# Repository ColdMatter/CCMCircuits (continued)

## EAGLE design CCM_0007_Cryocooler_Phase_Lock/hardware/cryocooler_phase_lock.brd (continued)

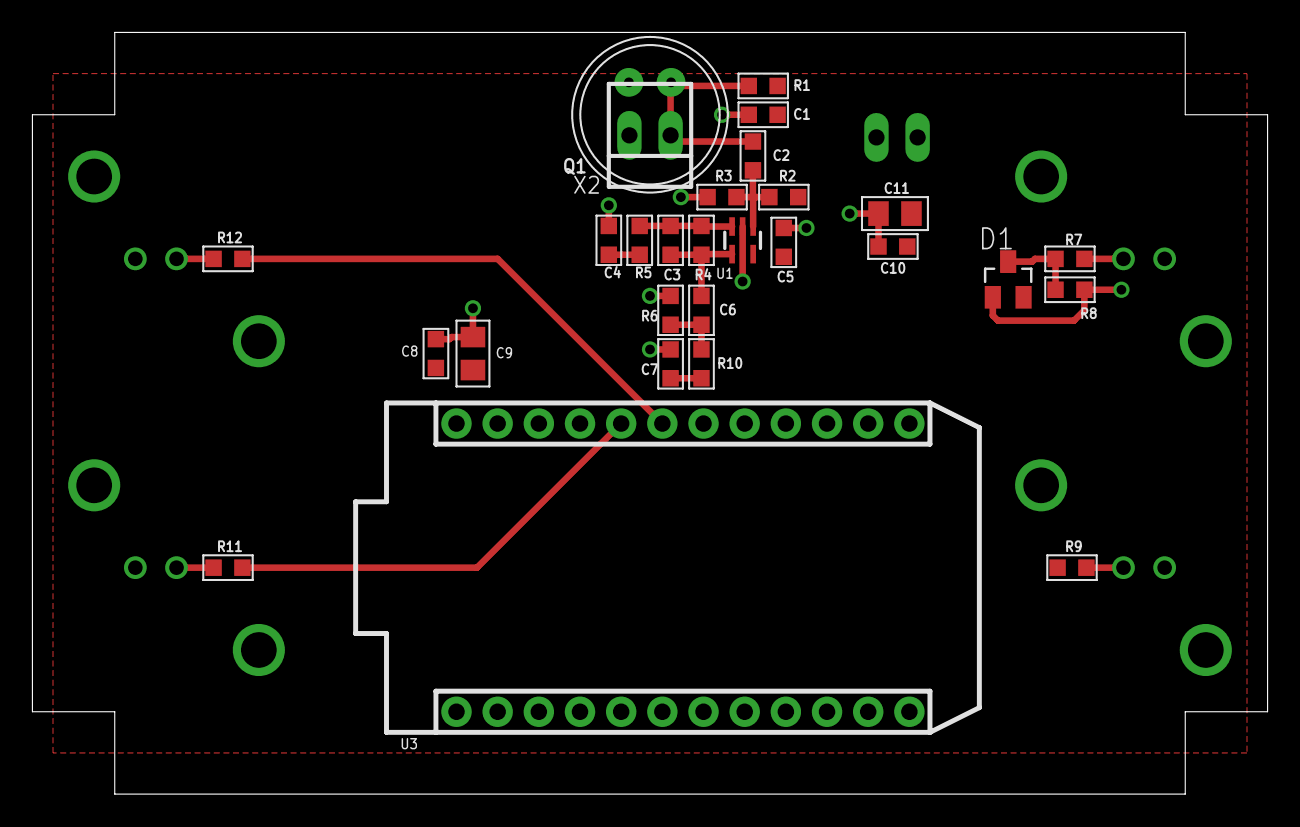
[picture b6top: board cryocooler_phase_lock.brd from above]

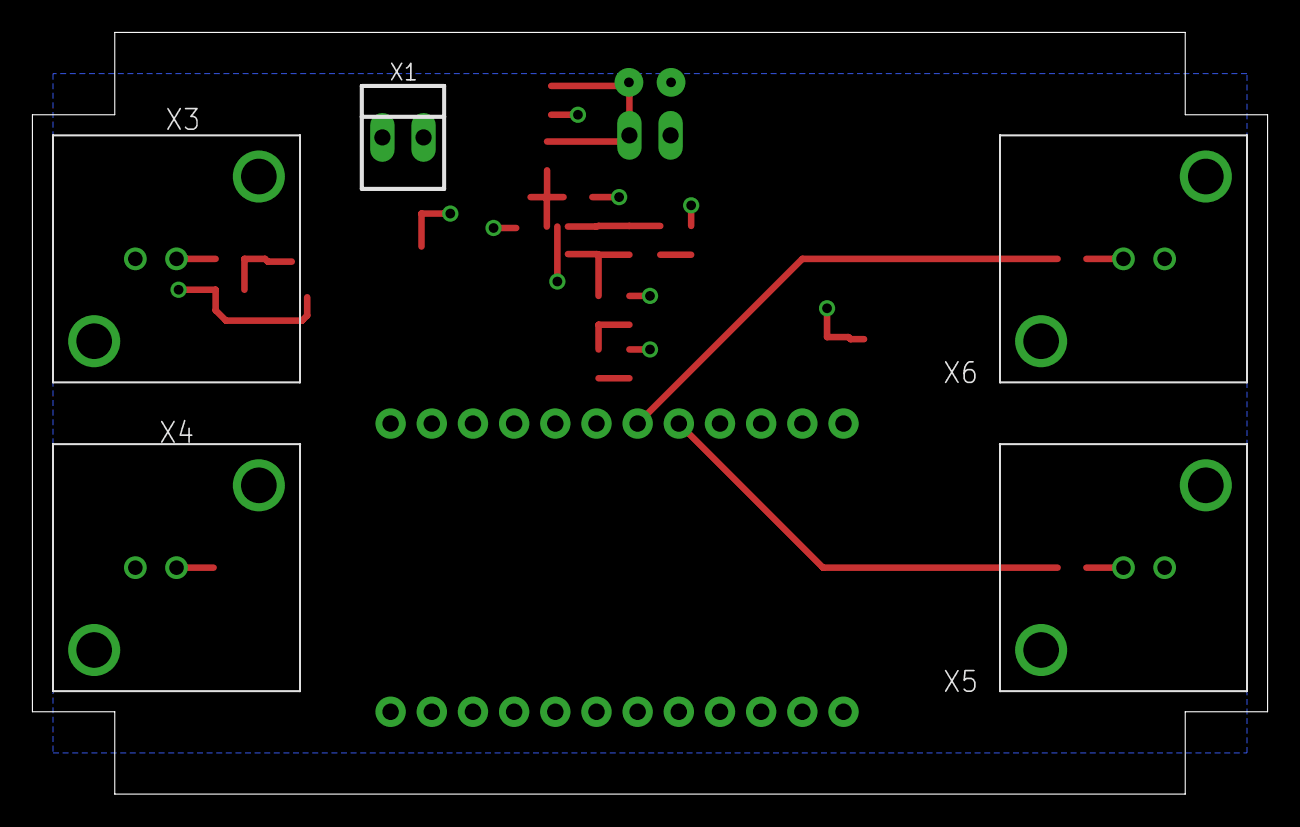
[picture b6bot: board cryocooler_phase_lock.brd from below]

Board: 2 copper layers, 76.2 x 47.0 mm, 33 parts (5 on the bottom side), 17 nets.
